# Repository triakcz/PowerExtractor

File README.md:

PowerExtractor
==============

GPL MPPT Regulator for bike (development prototype)

This is not finished project in development. Using Arduino to maximize power extracted from dynamo hub or solar panels ... yes it is so universal. Prototype tests shown power output of 8Watts @ 40km/h. Conversion efficiency is about 90% measured after initial rectification).

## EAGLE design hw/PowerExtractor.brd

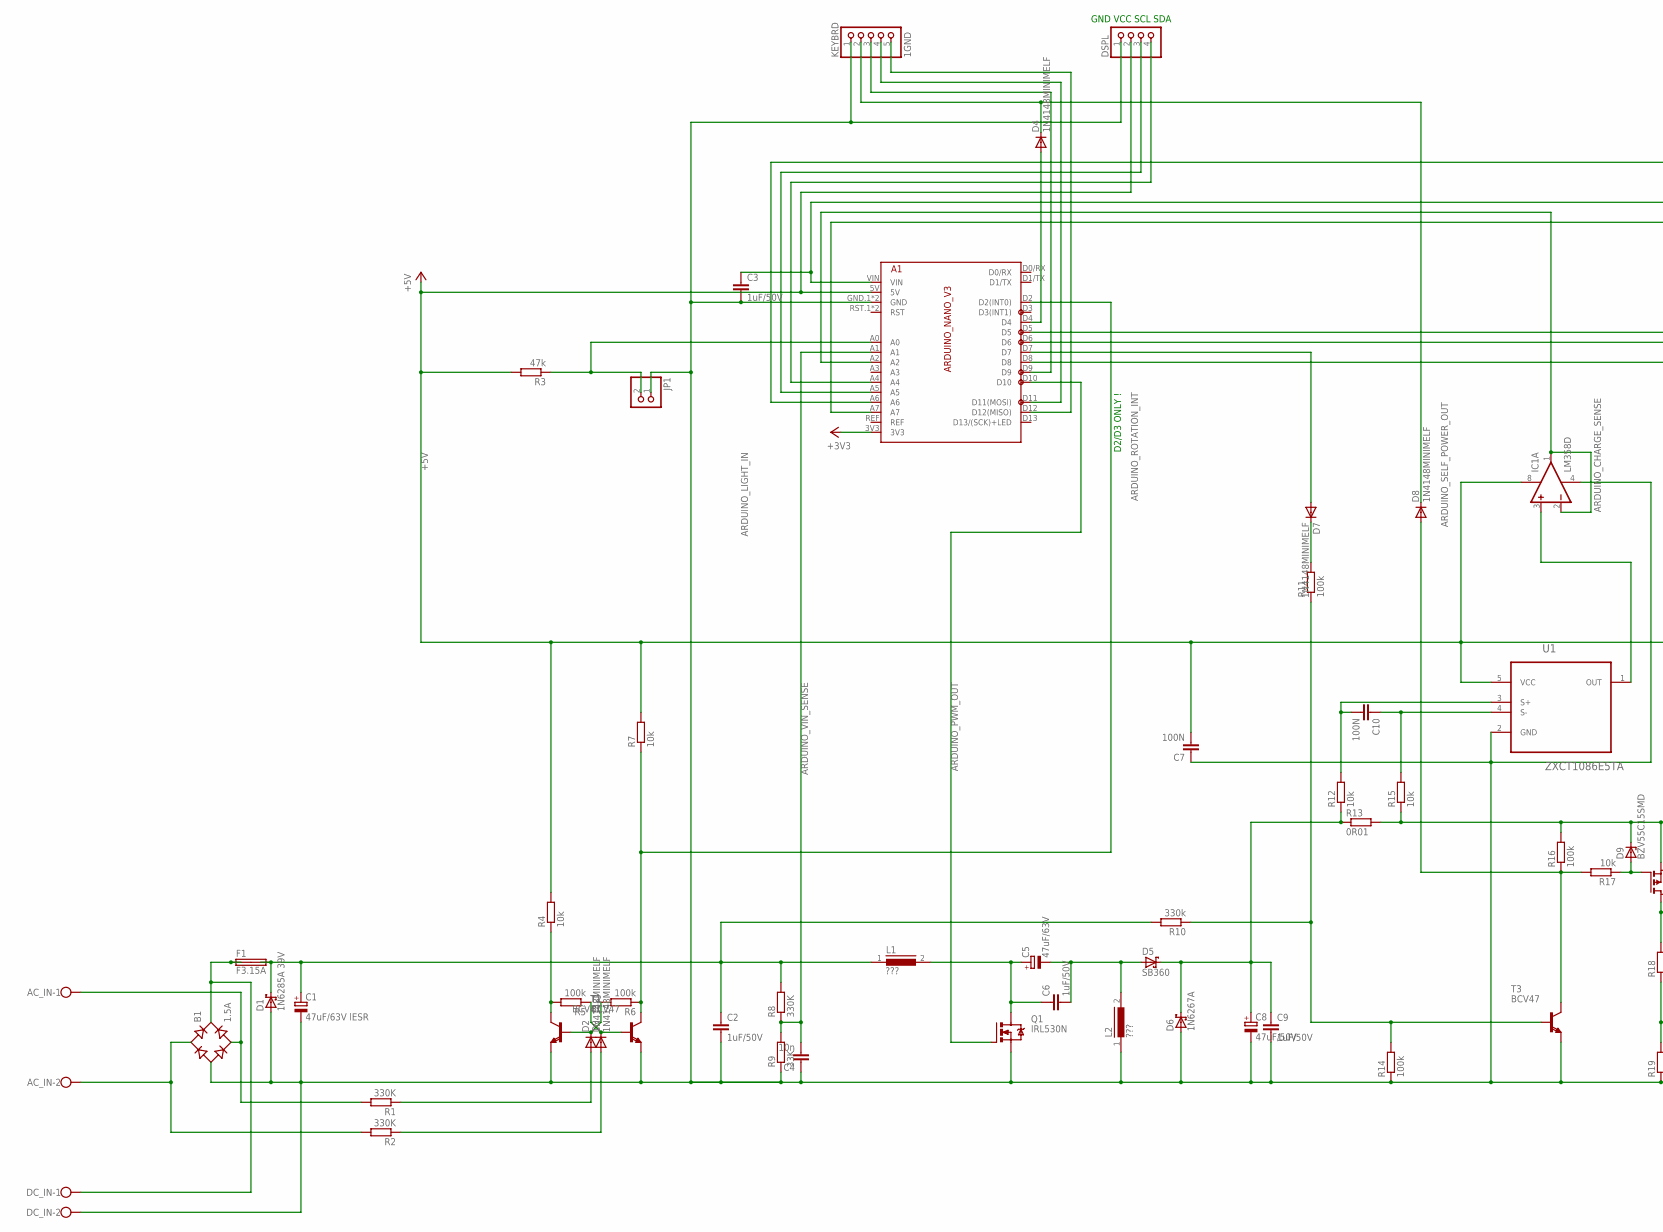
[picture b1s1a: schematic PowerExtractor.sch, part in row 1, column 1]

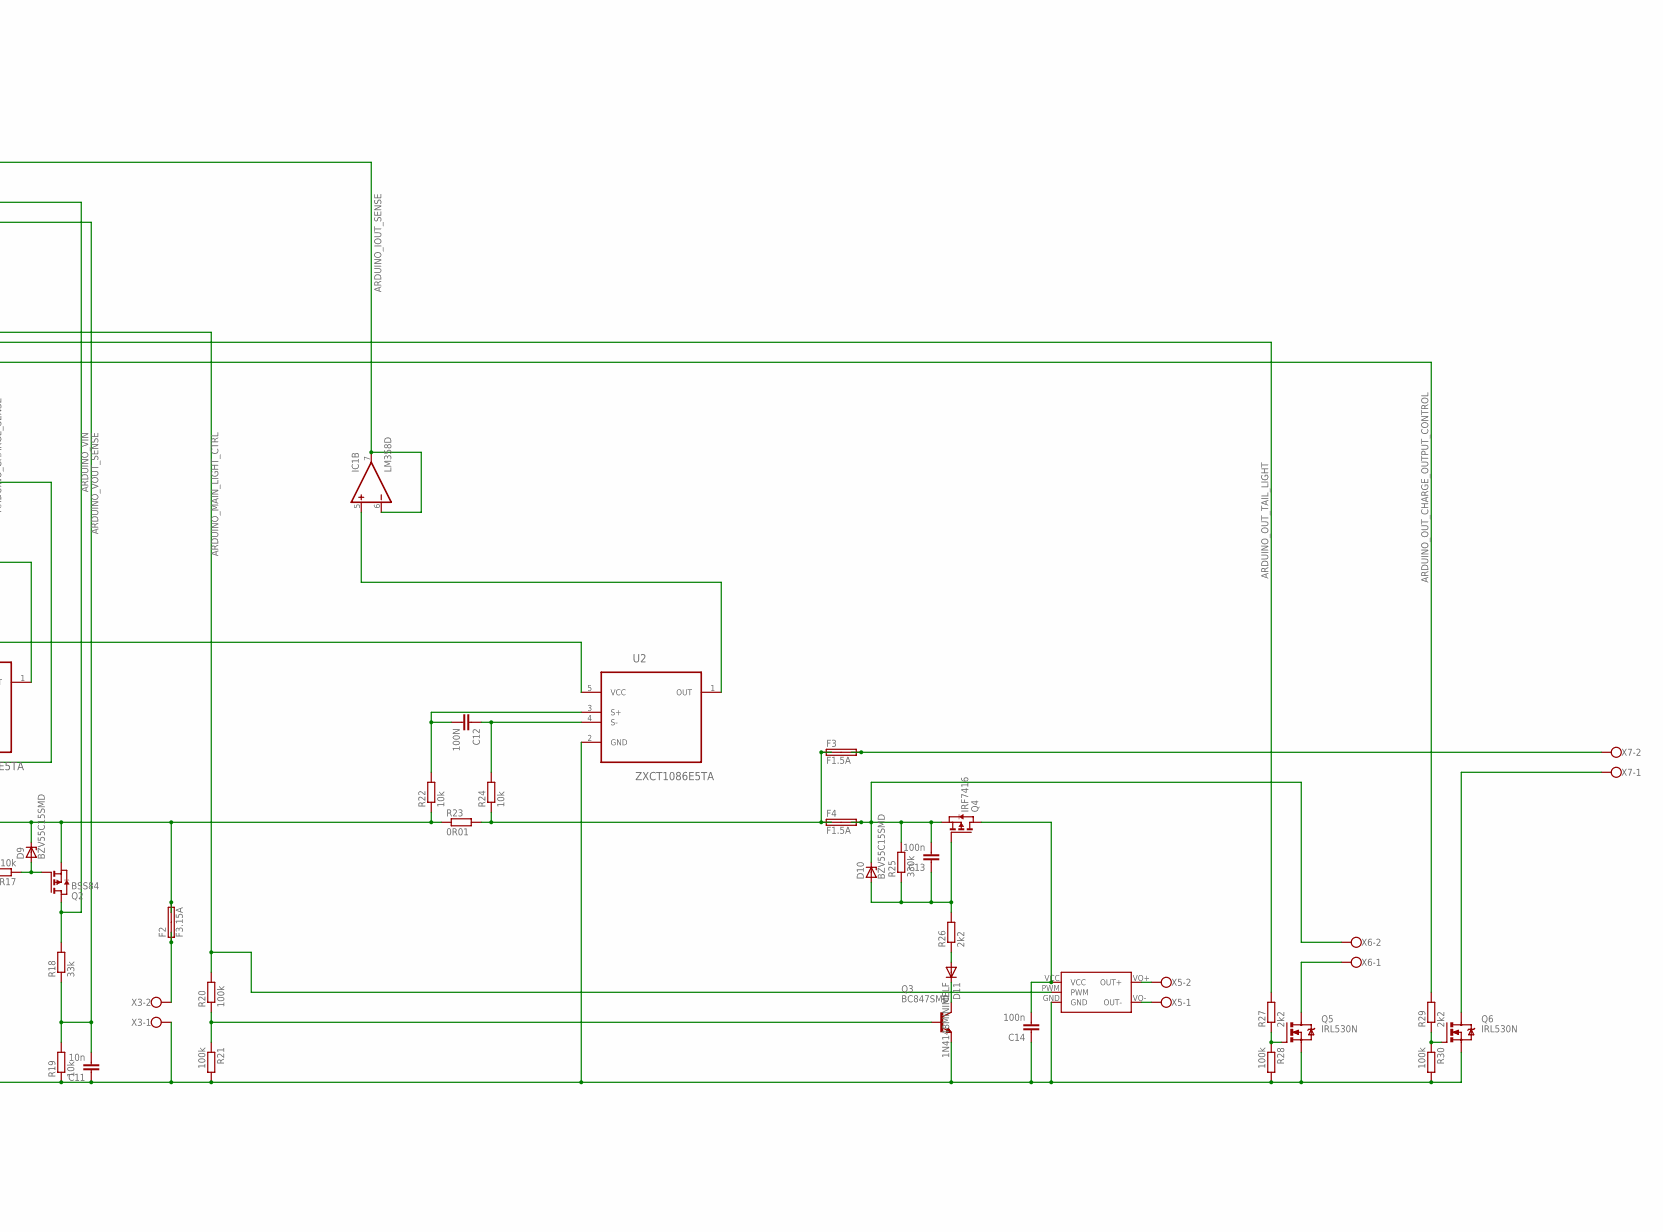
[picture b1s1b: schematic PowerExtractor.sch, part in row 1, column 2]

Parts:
A1: ARDUINO_NANO_V3
AC_IN: W237-102
B1: 1.5A; RB1A
C1: 47uF/63V lESR; E5-8,5
C2, C3, C6, C9: 1uF/50V; C0805
C4, C11: 10n; C0805
C5: 47uF/63V; E5-8,5
C7, C10, C12: 100N; C0805
C8: 47uF/50V; E5-8,5
C13, C14: 100n; C0805
D1: 1N6285A 39V; C4111-15
D2, D3, D4, D7, D8, D11: 1N4148MINIMELF; SOD80C
D5: SB360; C4111-15
D6: 1N6267A; C4111-15
D9, D10: BZV55C15SMD; SOD80C
DC_IN: W237-102
DSPL: PINHD-1X4; 1X04
F1, F2: F3.15A; SHK20L
F3, F4: F1.5A; SHK20L
IC1: LM358D; SO08
JP1: PINHD-1X2; 1X02
KEYBRD: 1GND; 1X05
L1, L2: ???; SFT1030
Q1, Q5, Q6: IRL530N; TO220BV
Q2: BSS84; SOT23
Q3: BC847SMD; SOT23
Q4: IRF7416; SO-8
R1, R2, R8: 330K; M0805
R3: 47k; 0207/10
R4, R12, R15, R17, R19, R22, R24: 10k; M0805
R5, R20: 100k; 0207/10
R6, R30: 100k; R0805
R7: 10k; R0805
R9: 33K; R0805
R10: 330k; R0805
R11, R14, R16, R21, R28: 100k; M0805
R13, R23: 0R01; M1206
R18: 33k; M0805
R25: 330k; M0805
R26: 2k2; M0805
R27, R29: 2k2; 0207/10
T1, T2, T3: BCV47; SOT23
U1, U2: ZXCT1086E5TA; SOT95P280X130-5N
X3, X5, X6, X7: W237-102
X4: LDD700L; LDD_700L

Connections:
+3V3: A1.3V3
+5V: A1.5V, C7.2, DSPL.2, IC1.8 (V+), R3.2, R4.2, R7.2, U1.5 (VCC), U2.5 (VCC)
+OUT: F3.2A, F3.2B, X7.2
ARDUINO_CHARGE_SENSE: A1.A2, IC1.1 (OUT), IC1.2 (-IN)
ARDUINO_IOUT_SENSE: A1.A6, IC1.6 (-IN), IC1.7 (OUT)
ARDUINO_LIGHT_IN: A1.A0, JP1.2, R3.1
ARDUINO_MAIN_LIGHT_CTRL: A1.D5, R20.2, X4.PWM
ARDUINO_OUT_CHARGE_OUTPUT_CONTROL: A1.D8, R29.2
ARDUINO_OUT_TAIL_LIGHT: A1.D6, R27.2
ARDUINO_PWM_OUT: A1.D10, Q1.G
ARDUINO_ROTATION_INT: A1.D2 (D2(INT0)), R6.1, R7.1, T2.3 (C)
ARDUINO_SELF_POWER_OUT: A1.D7, D7.A
ARDUINO_VIN: A1.VIN, C3.1, Q2.3 (D), R18.2
ARDUINO_VIN_SENSE: A1.A1, C4.2, R8.1, R9.2
ARDUINO_VOUT_SENSE: A1.A7, C11.2, R18.1, R19.2
BAT+: F2.1A, F2.1B, X3.2
BAT+FUSED: D9.C, F2.2A, F2.2B, Q2.2 (S), R13.2, R15.1, R16.2, R22.1, R23.1
DISPLAY_SCL: A1.A5, DSPL.3
DISPLAY_SDA: A1.A4, DSPL.4
GND: A1.GND.1 (GND), A1.GND.2 (GND), B1.-, C1.-, C2.2, C3.2, C4.1, C7.1, C8.-, C9.2, C11.1, C14.1, D1.A, D6.A, DC_IN.2, DSPL.1, IC1.4 (V-), JP1.1, KEYBRD.1, L2.1, Q1.S, Q3.2 (E), Q5.S, Q6.S, R9.1, R14.1, R19.1, R21.2, R28.2, R30.2, T1.2 (E), T2.2 (E), T3.2 (E), U1.2 (GND), U2.2 (GND), X3.1, X4.GND
HUB1: AC_IN.1, B1.AC2, R1.2
HUB2: AC_IN.2, B1.AC1, R2.2
LIGHTVCC: C13.2, D10.C, F4.2A, F4.2B, Q4.1 (S), Q4.2 (S), Q4.3 (S), R25.2, X6.2
unnamed: C10.2, R12.2, U1.3 (S+)
unnamed: C5.+, C6.1, L1.2, Q1.D
unnamed: C5.-, C6.2, D5.A, L2.2
unnamed: R10.1, R11.1, R14.2, T3.1 (B)
unnamed: IC1.3 (+IN), U1.1 (OUT)
unnamed: D4.C, D8.C, KEYBRD.2
unnamed: D9.A, Q2.1 (G), R17.1
unnamed: IC1.5 (+IN), U2.1 (OUT)
unnamed: D11.C, Q3.3 (C)
unnamed: B1.+, DC_IN.1, F1.1A, F1.1B
unnamed: D7.C, R11.2
unnamed: X4.VO+ (OUT+), X5.2
unnamed: C13.1, D10.A, Q4.4 (G), R25.1, R26.2
unnamed: X4.VO- (OUT-), X5.1
unnamed: C10.1, R15.2, U1.4 (S-)
unnamed: Q3.1 (B), R20.1, R21.1
unnamed: D11.A, R26.1
unnamed: C14.2, Q4.5 (D), Q4.6 (D), Q4.7 (D), Q4.8 (D), X4.VCC
unnamed: D8.A, R16.1, R17.2, T3.3 (C)
unnamed: Q5.G, R27.1, R28.1
unnamed: Q5.D, X6.1
unnamed: A1.D9, KEYBRD.3
unnamed: Q6.G, R29.1, R30.1
unnamed: Q6.D, X7.1
unnamed: D2.A, R1.1
unnamed: R4.1, R5.2, T1.3 (C)
unnamed: D2.C, R6.2, T1.1 (B)
unnamed: D3.C, R5.1, T2.1 (B)
unnamed: A1.D11 (D11(MOSI)), KEYBRD.4
unnamed: D3.A, R2.1
unnamed: A1.D12 (D12(MISO)), KEYBRD.5
unnamed: A1.D4, D4.A
unnamed: C12.2, R22.2, U2.3 (S+)
unnamed: C12.1, R24.2, U2.4 (S-)
OUT+SENSED: F3.1A, F3.1B, F4.1A, F4.1B, R23.2, R24.1
OUTPUT_TO_SENSE: C8.+, C9.1, D5.C, D6.C, R12.1, R13.1
VIN: C1.+, C2.1, D1.C, F1.2A, F1.2B, L1.1, R8.2, R10.2

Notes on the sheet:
D2/D3 ONLY !
GND VCC SCL SDA

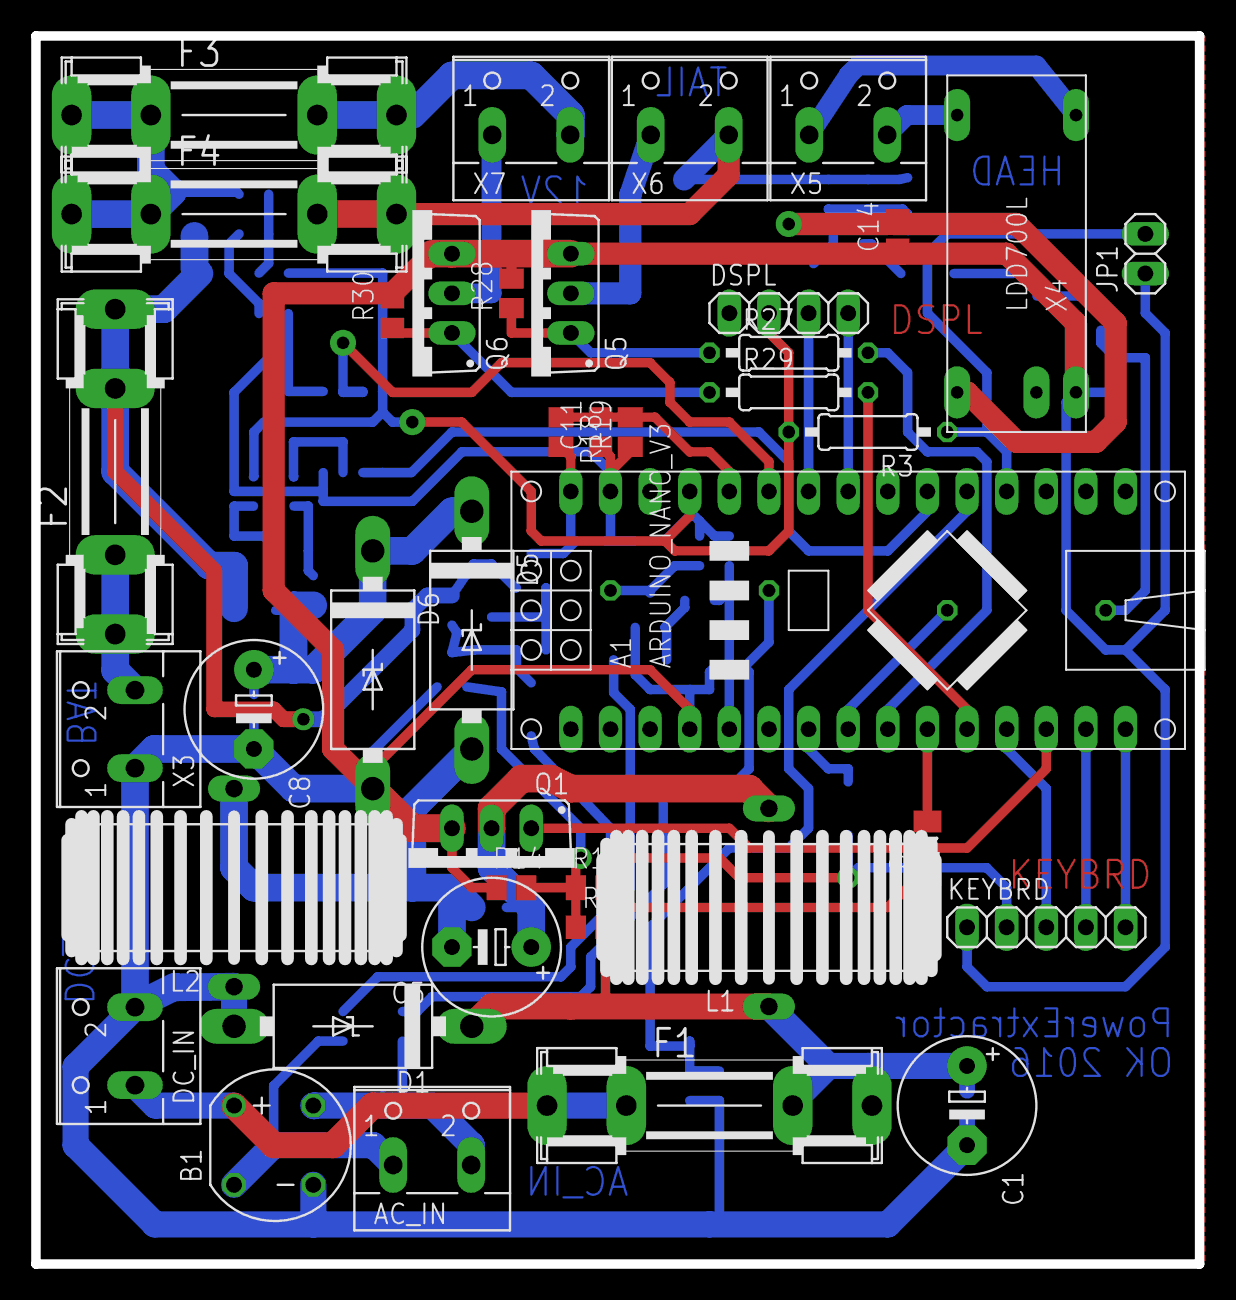
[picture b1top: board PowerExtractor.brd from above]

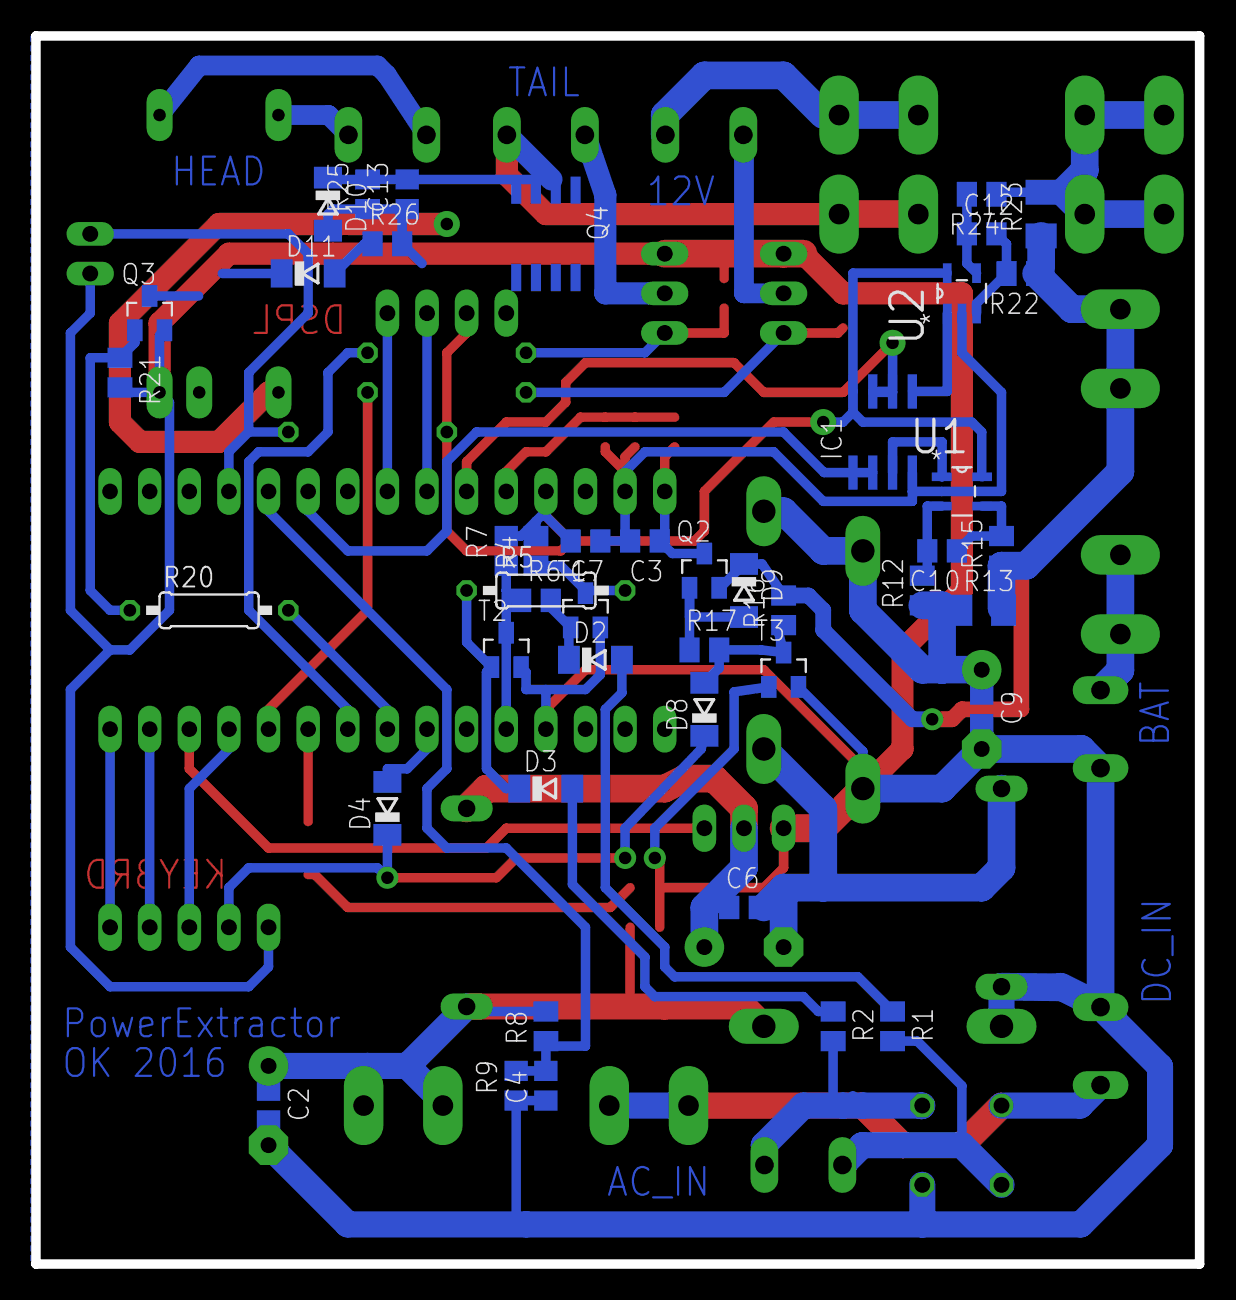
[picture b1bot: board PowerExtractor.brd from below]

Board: 2 copper layers, 74.6 x 78.7 mm, 85 parts (45 on the bottom side), 59 nets.

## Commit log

2013-05-15 Description and license
2013-05-15 First version of prototype firmware
2013-05-15 First version of MPPT prototype
2013-05-16 Experimentally switching USB power output with NXP630AD2T by UP/DOWN keys
2015-06-21 Modifications of schematic and added library with components
2015-06-22 Add 5V USB out, 12V out, both controlled by arduino
2015-06-23 Arduino Nano V3 in library
2015-10-12 Connected arduino in schematic
2016-03-20 Adding latest version
2016-03-20 Routing of board
2016-03-20 Routing
2016-03-21 Refactored layout
2016-03-22 Completely routed
2016-03-23 set reasonable width of power lines
2016-04-03 Added spice netlist for new speedsense circuit
2016-04-05 Adding BCV47 to library
2016-04-05 Fixed speed sense circuit
2016-04-07 Shifted speed sense circuit under MCU
2016-04-07 Refactored PCB layout
2016-04-10 Added prefix to custom devices in eagle library
2016-04-10 Updated library - arduino removed holes from dimension layer
2016-04-10 Fixed upside down in layout2 cam job for PE
2016-04-10 layout2 fix
2016-04-11 Fixed values and types of few parts
2016-04-14 Fixed BSS84 pinout
2016-04-21 Multiple firmware parts
    - Manual PWM control
    - Voltage read and display functions
    - Keyboard handling method
    - Added interrupts for periodic actions
    - Turnofftimer skeleton
2016-04-21 Fixed wrongly placed resistor (0207 placed on bottom side)
2016-06-12 Fixing various bugs
2016-06-13 multiple fixes
2016-06-13 refactoring
2020-01-12 backup all
2020-01-12 wip kicad
2020-01-14 Done
2020-05-10 PE2020
